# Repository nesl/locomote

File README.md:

# LocoMote: AI-driven Sensor Tags for Fine-Grained Undersea Localization and Sensing

## Paper
https://ieeexplore.ieee.org/abstract/document/10494218/

## Summary
Long-term and fine-grained maritime localization and sensing is challenging due to sporadic connectivity, constrained power budget, limited footprint, and hostile environment. In this paper, we present the design considerations and implementation of LocoMote, a rugged ultra-low-footprint undersea sensor tag with on-device AI-driven localization, online communication, and energy-harvesting capabilities. LocoMote uses on-chip (< 30 kB) neural networks to track underwater objects within 3 meters with ~6 minutes of GPS outage from 9DoF inertial sensor readings. The tag streams data at 2-5 kbps (< 10^-3 bit error rate) using piezo-acoustic ultrasonics, achieving underwater communication range of more than 50 meters while allowing up to 55 nodes to concurrently stream via randomized time-division multiple access. To recharge the battery during sleep, the tag uses an aluminum-air salt water energy harvesting system, generating upto 5 mW of power. LocoMote is ultra-lightweight (< 50 grams), tiny (32x32$x10 mm^3), consumes low power (~330 mW peak), and comes with a suite of high-resolution sensors. We highlight the hardware and software design decisions, implementation lessons, and the real-world performance of our tag versus existing oceanic sensing technologies. 

## Code Architecture
- ```encasement```: contains the ```.stl``` CAD files for the EPU-40 encasement and resin base.
- ```pcb```: contains the altium pcb design files for the main circuit board, and eagle pcb design files for the offline battery charger and pressure sensor board. PCB schematic and board design images are also provided.
- ```software```: contains code for: (a) data logging from all the sensors into the flash, also contains code to toggle data recovery modes from a computer using a Python script (```data_logger_demo```); (b) communication stack for the transmitter and receiver (```piezo_OOK_demo```); (c) PWM demo for piezo (```piezo_PWM_demo```); (d) GPS data logging and power measurement (```GPS```); (e) repository link for developing neural inertial navigation algorithms, as well as Marina Del Rey deployment IMU, GPS dataset; an importer is provided for the dataset (```neural_inertial_navigation```).

## Required items
- Altium Designer (21.x.x or higher) (https://www.altium.com/altium-designer/).
- AutoDesk Eagle (9.6.2 or higher) (https://www.autodesk.com/products/eagle/overview)
- TinkerCad (https://www.tinkercad.com/).
- For developing neural inertial navigation algorithms, check the requirements in ```software/neural_inertial_navigation/tinyodom```.
- MATLAB with all toolboxes installed (R2020a or better).
- Arduino IDE (https://www.arduino.cc/en/software/) with STM32 Core installed (https://github.com/stm32duino/Arduino_Core_STM32). The Arduino libraries required are listed in ```software/arduino_lib_links.txt```.
- Audacity (https://www.audacityteam.org/)
- Hardware: Check the pcb design files and the paper for list of hardware required and purchase links.

## Citation
Please cite this as:

Swapnil Sayan Saha, Caden Davis, Sandeep Singh Sandha, Junha Park, Joshua Geronimo, Luis Antonio Garcia and Mani Srivastava, "LocoMote: AI-driven Sensor Tags for Fine-Grained Undersea Localization and Sensing", in IEEE Sensors Journal, vol. 24, no. 10, pp. 16999-17018, 15 May 2024, IEEE.

## Acknowledgements
 This work was sponsored in part by: the IoBT REIGN Collaborative Research Alliance funded by the Army Research Laboratory under Cooperative Agreement W911NF-17-2-0196; the Air Force Office of Scientific Research under award FA9550-22-1-0193; the CONIX Research Center, one of the centers in Joint University Microelectronics Program, a Semiconductor Research Corporation program sponsored by the Defense Advanced Research Projects Agency; and, the King Abdullah University of Science and Technology through its Sensor Innovation research program.

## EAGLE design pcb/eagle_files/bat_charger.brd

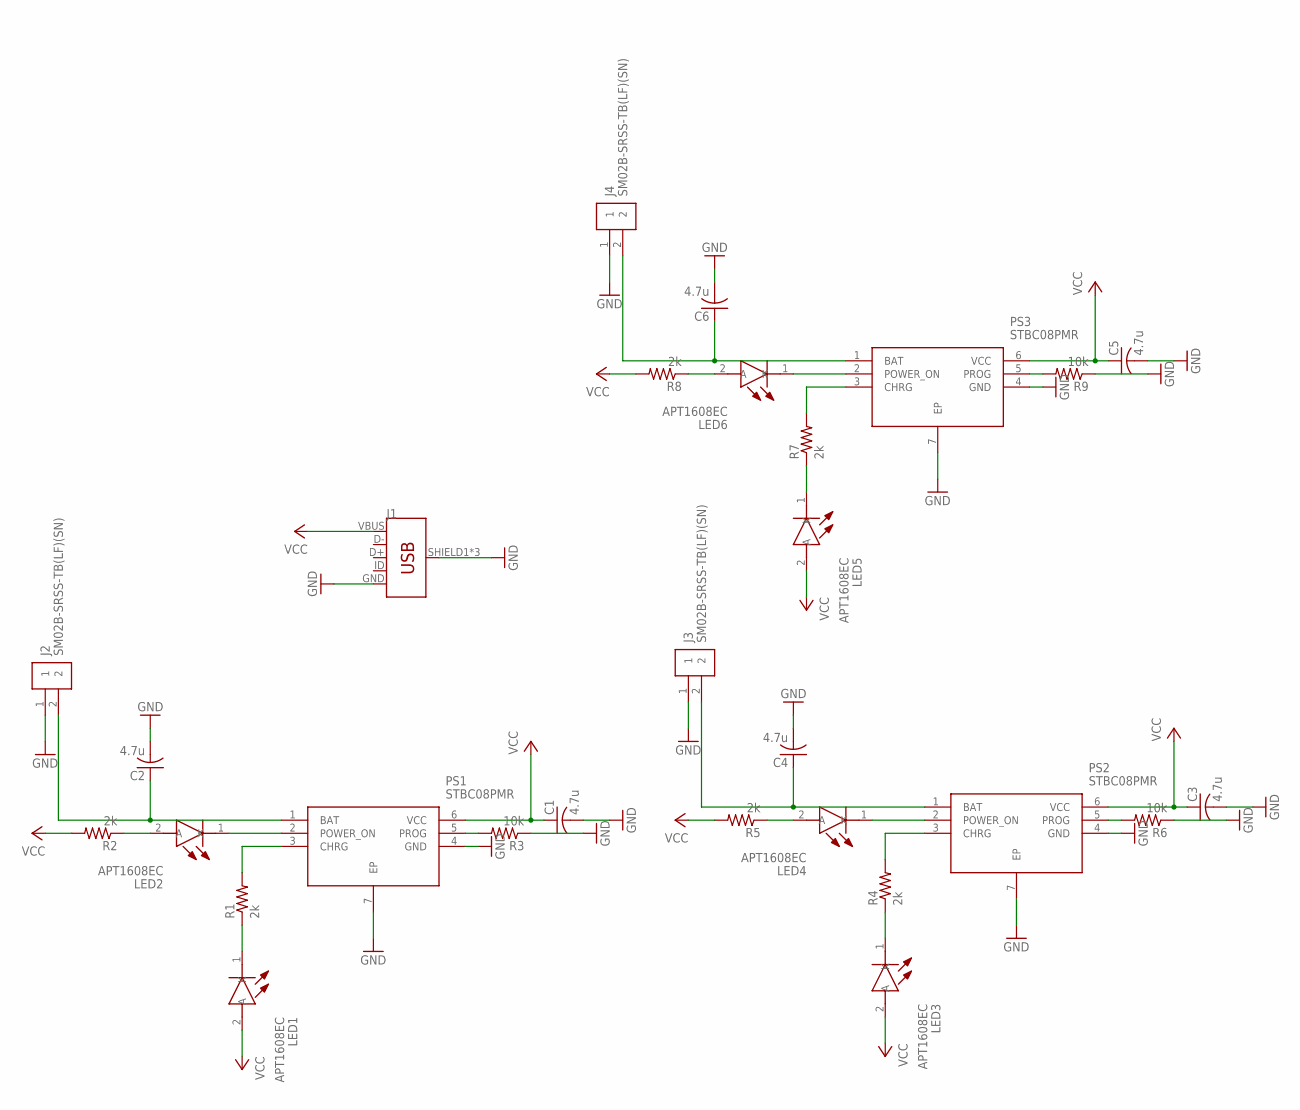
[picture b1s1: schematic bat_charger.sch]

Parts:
C1, C2, C3, C4, C5, C6: 4.7u; C0603
J1: USB_MICRO-B_FEMALE-SMT; USB-B-MICRO-SMD
J2, J3, J4: SM02B-SRSS-TB(LF)(SN)
LED1, LED2, LED3, LED4, LED5, LED6: APT1608EC; LEDC1608X85N
PS1, PS2, PS3: STBC08PMR; SON95P300X300X100-7N
R1, R2, R4, R5, R7, R8: 2k; R0603
R3, R6, R9: 10k; R0603

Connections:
GND: C1.2, C2.2, C3.2, C4.2, C5.2, C6.2, J1.GND, J1.SHIELD1 (SHIELD), J1.SHIELD2 (SHIELD), J1.SHIELD3 (SHIELD), J2.1, J3.1, J4.1, PS1.4 (GND), PS1.7 (EP), PS2.4 (GND), PS2.7 (EP), PS3.4 (GND), PS3.7 (EP), R3.1, R6.1, R9.1
unnamed: PS1.3 (CHRG), R1.2
unnamed: LED1.1 (K), R1.1
unnamed: C2.1, J2.2, PS1.1 (BAT)
unnamed: LED2.1 (K), PS1.2 (POWER_ON)
unnamed: LED2.2 (A), R2.1
unnamed: PS1.5 (PROG), R3.2
unnamed: PS2.3 (CHRG), R4.2
unnamed: LED3.1 (K), R4.1
unnamed: LED4.1 (K), PS2.2 (POWER_ON)
unnamed: LED4.2 (A), R5.1
unnamed: PS2.5 (PROG), R6.2
unnamed: C4.1, J3.2, PS2.1 (BAT)
unnamed: PS3.3 (CHRG), R7.2
unnamed: LED5.1 (K), R7.1
unnamed: LED6.1 (K), PS3.2 (POWER_ON)
unnamed: LED6.2 (A), R8.1
unnamed: PS3.5 (PROG), R9.2
unnamed: C6.1, J4.2, PS3.1 (BAT)
VCC: C1.1, C3.1, C5.1, J1.VBUS, LED1.2 (A), LED3.2 (A), LED5.2 (A), PS1.6 (VCC), PS2.6 (VCC), PS3.6 (VCC), R2.2, R5.2, R8.2

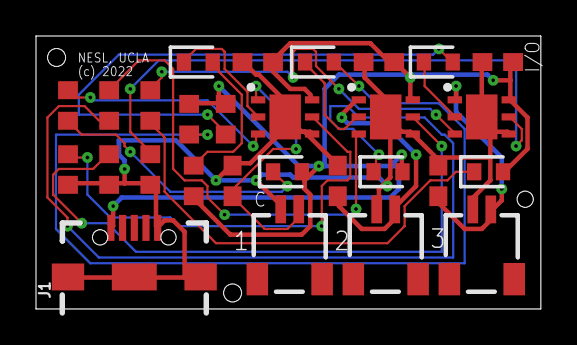
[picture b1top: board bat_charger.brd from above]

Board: 2 copper layers, 28.0 x 15.2 mm, 28 parts (0 on the bottom side), 20 nets.

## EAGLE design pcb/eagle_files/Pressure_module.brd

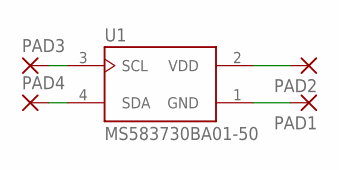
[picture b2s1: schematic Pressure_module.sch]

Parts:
PAD1, PAD2, PAD3, PAD4: 1,6/0,8
U1: MS583730BA01-50; TE_MS583730BA01-50

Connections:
unnamed: PAD3.1, U1.3 (SCL)
unnamed: PAD4.1, U1.4 (SDA)
unnamed: PAD2.1, U1.2 (VDD)
unnamed: PAD1.1, U1.1 (GND)

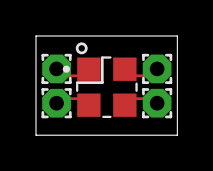
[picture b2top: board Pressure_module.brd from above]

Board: 2 copper layers, 7.9 x 5.5 mm, 5 parts (0 on the bottom side), 4 nets.

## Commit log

2022-11-22 added mech pcb soft
2022-11-22 added mdr deployment data
2022-11-22 added bat charger and pressure boards
2022-11-23 added mdr gps data
2022-11-25 updated logger
2022-11-26 add gps code
2022-11-27 add gps .txt data
2022-11-27 add tinyodom repo
2022-11-27 added mdr data importer
2022-11-27 added license
2022-11-27 update mdr data utils

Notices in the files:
pcb/eagle_files/bat_charger.brd:
(c) 2022
(c) 2022, NESL, UCLA
parts and their libraries:
SparkFun-Connectors: Licensing: Creative Commons ShareAlike 4.0 International - https://creativecommons.org/licenses/by-sa/4.0
